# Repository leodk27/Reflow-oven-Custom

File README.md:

# Reflow Oven Controller  

### KES – Kwas Engineering Solutions  

---

## Overview

This is a controller for a reflow oven.  

---

## System

The system has three parts:

- Measurement (temperature)  
- Control (microcontroller)  
- Power switching (heater)  

---

## Hardware

- Microcontroller  
- Thermocouple interface  
- Triac switching stage  
- Power supply (internal and external)  

---

## Firmware

- Runs the temperature profile  
- Handles faults  
- Communicates over custom RJ45 service port  

---

## Safety

- High and low voltage are separated  
- Layout respects clearance  
- Faults lead to shutdown  

---

## Structure

- `/KICAD reflow-oven` — KiCad files  
- `/firmware` — code  
- `/docs` — notes  

---

## License

See LICENSE file.

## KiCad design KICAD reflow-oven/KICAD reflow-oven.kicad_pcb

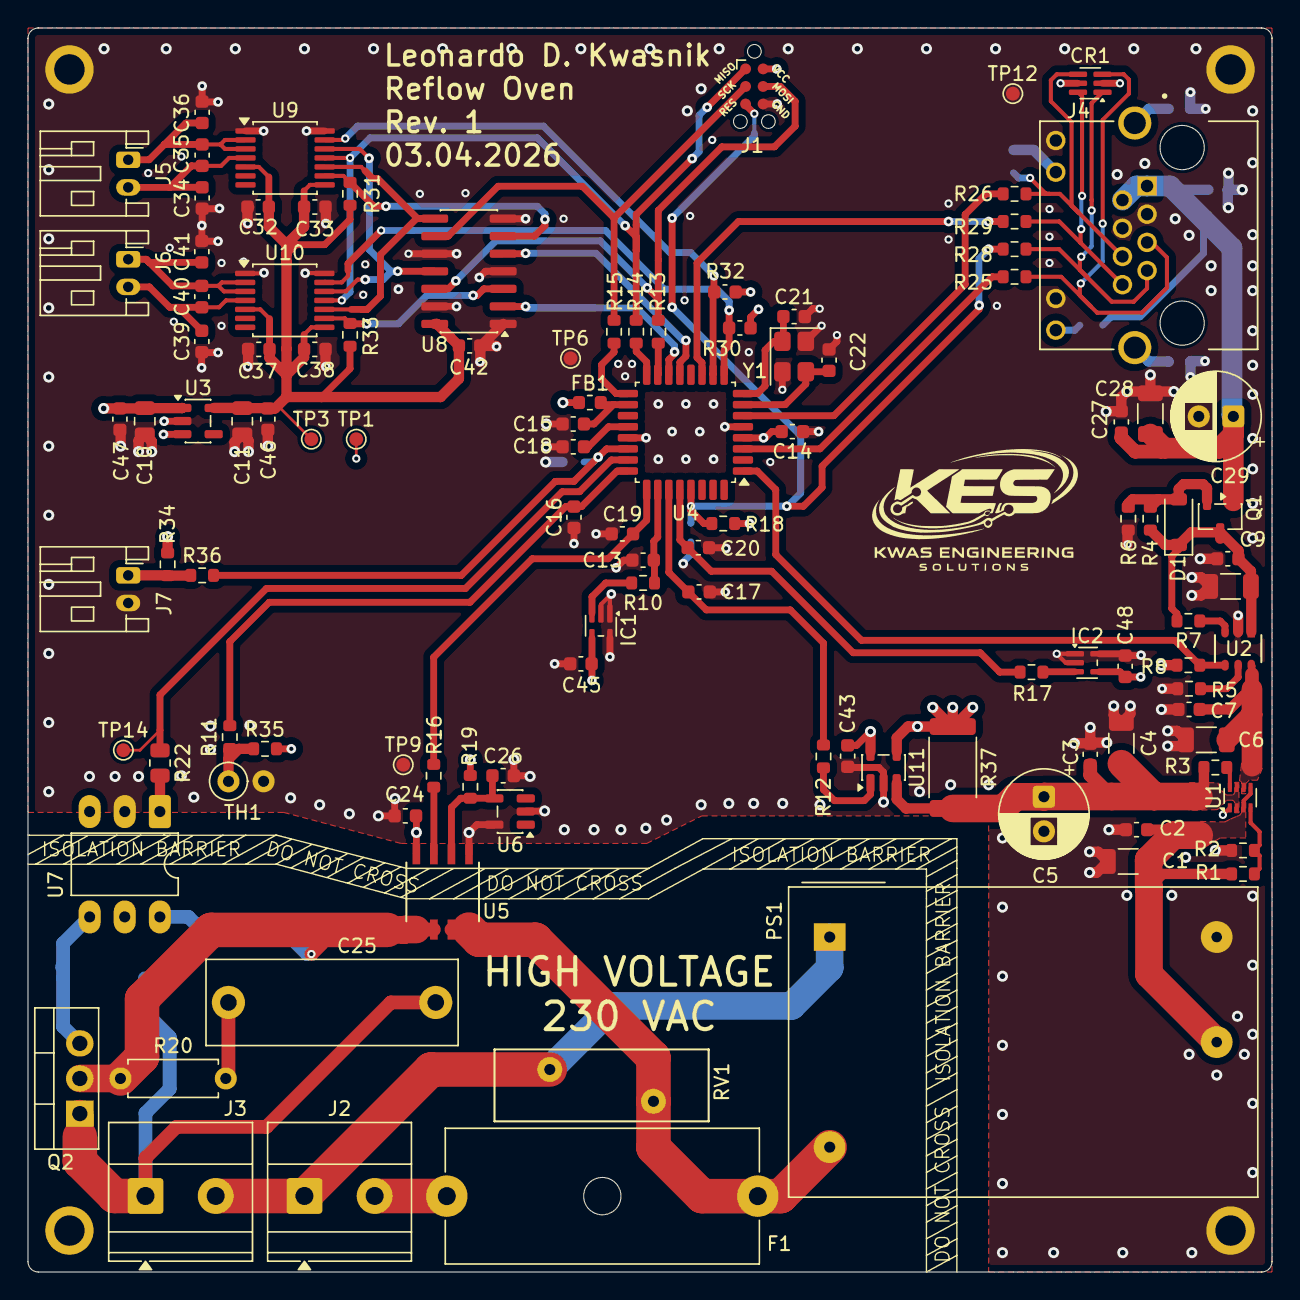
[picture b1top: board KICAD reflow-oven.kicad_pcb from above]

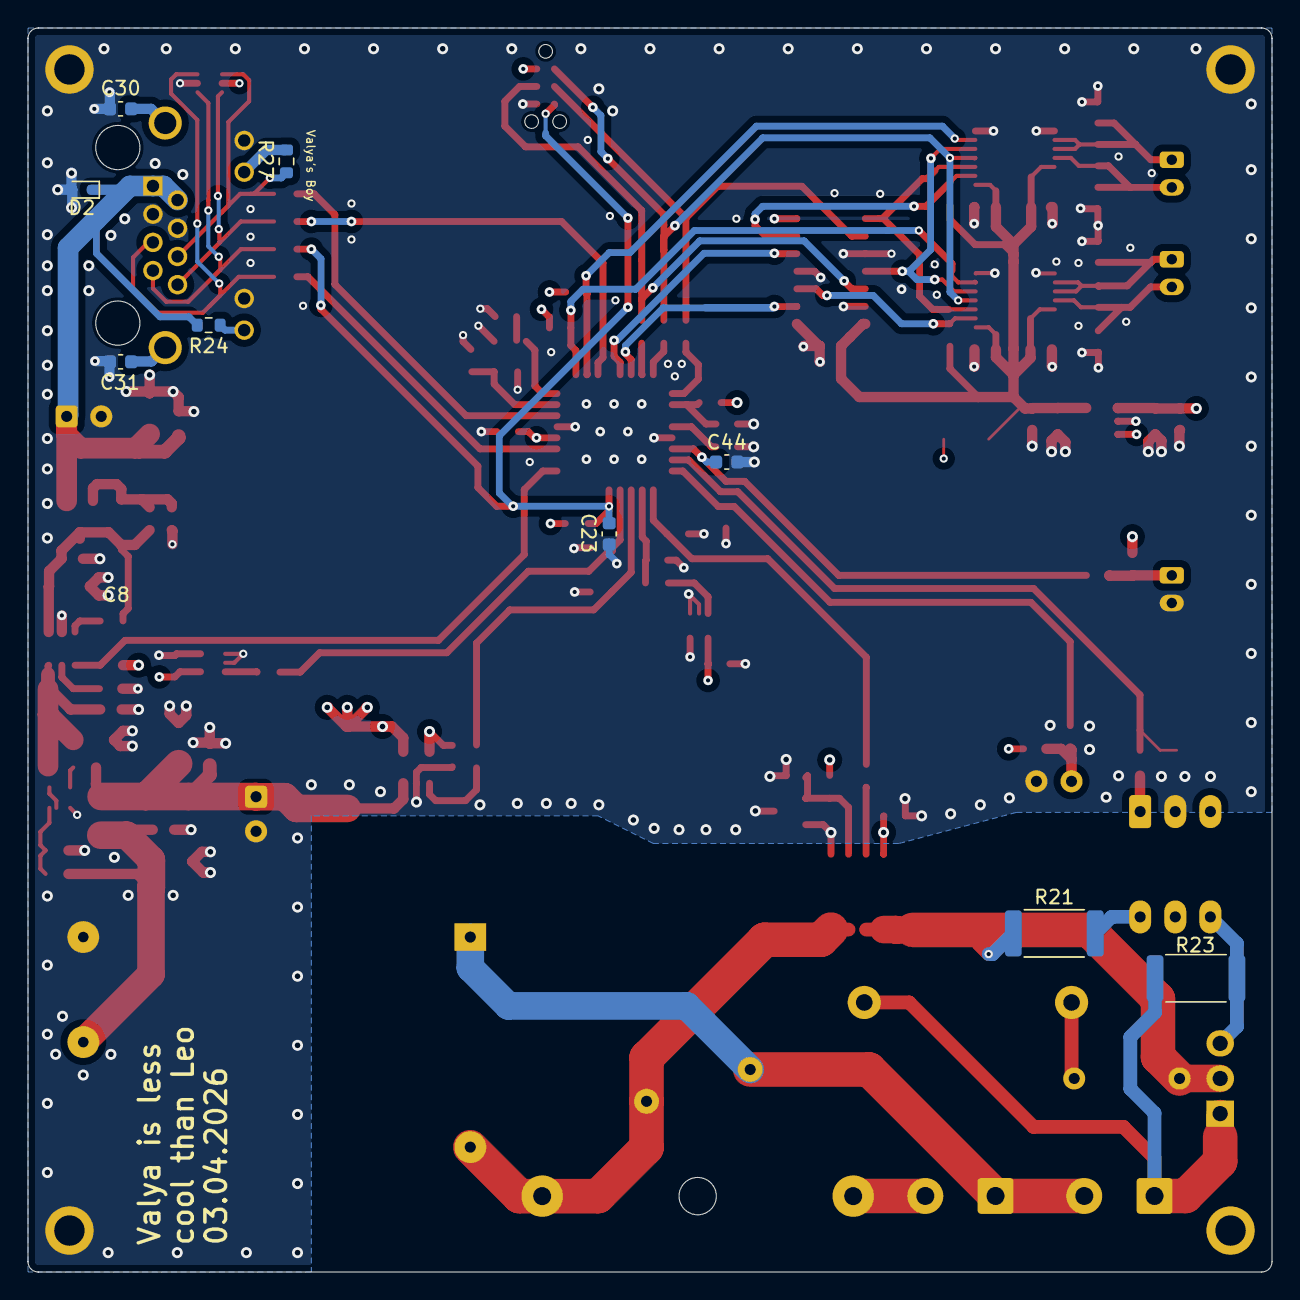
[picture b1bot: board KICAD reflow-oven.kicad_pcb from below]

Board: 4 copper layers, 90.0 x 90.0 mm, 124 parts (9 on the bottom side), 71 nets.

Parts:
C1, C4, C6, C8, C28: 10u; C_1206_3216Metric
C2, C3, C7, C9, C14, C15, C18, C24, C26, C27, C32, C33, C35, C37, C38, C40, C42, C43, C44, C45, C46, C47, C48: 100n; C_0603_1608Metric
C5, C29: 100u; CP_Radial_D6.3mm_P2.50mm
C10, C11: 1u; C_0805_2012Metric
C13, C16, C17, C19, C20, C34, C36, C39, C41: 10n; C_0603_1608Metric
C21, C22: 22p; C_0603_1608Metric
C23, C30, C31: 4.7n; C_0603_1608Metric
C25: 100n; C_Rect_L18.0mm_W6.0mm_P15.00mm_FKS3_FKP3
CR1: RCLAMP0504FBTCT; SOT-363_SC-70-6
D1: 6.8V; D_SOD-123
D2: ESD5Z5V; D_SOD-523
F1: Fuse; Fuseholder_Cylinder-5x20mm_Schurter_0031_8201_Horizontal_Op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
FB1: 600 @ 100M; L_0603_1608Metric
H1, H2, H3, H4: MountingHole_Pad; MountingHole_2.2mm_M2_ISO7380_Pad
IC1, IC2: TMP235AEDCKRQ1; SOT-353_SC-70-5
J1: KES-POGO_ISP_HEADER; KES_POGO_ISP_2x03_P1.27mm_Vertical
J2, J3: Screw_Terminal_01x02; TerminalBlock_Phoenix_MKDS-1,5-2-5.08_1x02_P5.08mm_Horizont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
J4: RJ45_LED_Shielded_SH1_SH2; ADAMTECH_MTJ-88ARX1-FSM-LG
J5, J6, J7: JST_PH; JST_PH_S2B-PH-K_1x02_P2.00mm_Horizontal
PS1: IRM-02-5; Converter_ACDC_MeanWell_IRM-02-xx_THT
Q1: PMOS; SOT-23-3
Q2: BTA16-600BW; TO-220-3_Vertical
R1: 360k; R_0603_1608Metric
R2, R4, R18: 100k; R_0603_1608Metric
R3, R6, R7, R8, R31, R33, R34, R35: 10k; R_0603_1608Metric
R5, R24, R27: 1k; R_0603_1608Metric
R10, R11, R12, R13, R14, R15, R16, R17, R25, R26, R28, R29: 100; R_0603_1608Metric
R19: 2.2k; R_0603_1608Metric
R20: 100; R_Axial_DIN0207_L6.3mm_D2.5mm_P7.62mm_Horizontal
R21, R23: 360; R_2512_6332Metric
R22: 220; R_0805_2012Metric
R30, R32: 10k; C_0603_1608Metric
R36: 470; R_0603_1608Metric
R37: 20m; R_2512_6332Metric
RV1: Varistor; RV_Disc_D15.5mm_W5.2mm_P7.5mm
TH1: 10k NTC; R_Axial_DIN0207_L6.3mm_D2.5mm_P2.54mm_Vertical
TP1: TP_5V; TestPoint_Pad_D1.0mm
TP3: TP_3V3; TestPoint_Pad_D1.0mm
TP6, TP9, TP12: TP_GND; TestPoint_Pad_D1.0mm
TP14: TP_HEAT_F; TestPoint_Pad_D1.0mm
U1: TPS2116DRL; SOT-583-8
U2: AP2553W6-7; SOT26_DIO
U3: TLV75533PDBV; SOT-23-5
U4: ATmega328PB-A; TQFP-32_7x7mm_P0.8mm
U5: TMCS1100A2QDR; SOIC8_D_TEX
U6: LM4030-2.5/NOPB; SOT-23-5
U7: MOC3063M; DIP-6_W7.62mm_LongPads
U8: 74LVC125; SOIC-14_3.9x8.7mm_P1.27mm
U9, U10: MAX31856; TSSOP-14_4.4x5mm_P0.65mm
U11: INA180A1; SOT-23-5
Y1: 16MHz; Crystal_SMD_3225-4Pin_3.2x2.5mm

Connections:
+3V3: C11.1, C32.1, C33.1, C37.1, C38.1, C42.2, C46.1, R31.1, R33.1, TP3.1, U3.5 (OUT), U8.14 (VCC), U9.5 (AVDD), U9.8 (DVDD), U10.5 (AVDD), U10.8 (DVDD)
+5V: C10.1, C14.2, C24.1, C43.1, C45.1, C47.1, C48.1, CR1.5, FB1.2, IC1.4 (VDD), IC2.4 (VDD), J1.2 (VCC), R8.2, R18.1, R19.1, R30.1, R32.1, R34.1, R35.1, R37.1, TP1.1, U3.1 (IN), U3.3 (EN), U4.4 (VCC), U5.8 (VS), U11.4 (-), U11.5 (V+)
/5V_CURRENT: R12.2, U11.1
/5V_TOSHUNT: C3.1, C4.1, C5.1, R3.1, R37.2, U1.2 (VOUT), U1.7 (VOUT), U11.3 (+)
/BOARD_TEMP1: IC1.3 (VOUT), R10.2
/BOARD_TEMP2: IC2.3 (VOUT), R17.2
/DOOR_STATUS: C44.1, R36.2, U4.22 (PE3)
/General_sensors/TO_REED: J7.1, R34.2, R36.1
/HEAT_control: R22.1, TP14.1, U4.23 (PC0)
/MAINS_CURRENT: R16.2, U5.7 (VOUT)
/MCU/AREF: C18.2, U4.20 (AREF)
/MCU/AVCC: C15.2, FB1.1, U4.18 (AVCC)
/MCU/MCU_MISO: R14.2, U4.16 (PB4)
/MCU/MCU_MOSI: R13.2, U4.15 (PB3)
/MCU/MCU_SCK: R15.2, U4.17 (PB5)
/MCU/PC1_A: C16.2, R11.1, U4.24 (PC1)
/MCU/PC2_A: C19.2, R16.1, U4.25 (PC2)
/MCU/PC3_A: C13.2, R10.1, U4.26 (PC3)
/MCU/PC4_A: C17.2, R12.1, U4.27 (PC4)
/MCU/PC5_A: C20.2, R17.1, U4.28 (PC5)
/MCU/XTAL1: C22.1, U4.7 (XTAL1/PB6), Y1.3
/MCU/XTAL2: C21.1, U4.8 (XTAL2/PB7), Y1.1
/MCU_MISO_R: J1.1 (MISO), R14.1, U9.11 (SDO), U10.11 (SDO)
/MCU_MOSI_R: J1.4 (MOSI), R13.1, U8.12
/MCU_SCK_R: J1.3 (SCK), R15.1, U8.9
/Mains_switching/AC_L_FUSED: F1.1, PS1.2 (AC/L), RV1.1, U5.3 (IN-), U5.4 (IN-)
/Mains_switching/AC_L_IN: F1.2, J2.2
/Mains_switching/AC_L_TO_HEATER: C25.2, J3.1, Q2.1 (A1), R23.1
/Mains_switching/AC_L_TO_TRIAC: Q2.2 (A2), R20.1, R21.1, U5.1 (IN+), U5.2 (IN+)
/Mains_switching/AC_N: J2.1, J3.2, PS1.1 (AC/N), RV1.2
/Mains_switching/AC_T_GATE: Q2.3 (G), R23.2, U7.4
/Mains_switching/OPTOT_LED: R22.2, U7.1
/Mains_switching/OPTOT_OUT: R21.2, U7.6
/Mains_switching/SNUBBER: C25.1, R20.2
/Mains_switching/TMCS_VREF: C26.1, R19.2, U5.6 (VREF), U6.4 (VREF)
/Power_management/AP2553_EN: R7.1, U2.3 (EN)
/Power_management/AP2553_ILIM: R5.1, U2.5 (ILIM)
/Power_management/TPS_PR1: R1.2, R2.1, U1.4 (PR1)
/Power_management/TPS_ST: R3.2, U1.8 (ST)
/Power_management/VBUS_F1: C8.1, C9.1, D1.1 (K), Q1.3 (S), R4.1, R7.2, U2.1 (IN)
/Power_management/VBUS_F2: C6.1, C7.1, U1.6 (VIN2), U2.6 (OUT)
/Power_management/VBUS_PROT_G: D1.2 (A), Q1.2 (G), R4.2, R6.1
/RESET: C23.1, J1.5 (RESET), R18.2, R28.1, U4.29 (~RESET/PC6)
/RJ45_input/RJ45_LED_1: J4.12, R24.1
/RJ45_input/RJ45_LED_2: J4.10, R27.1
/RJ45_input/RJ45_RESET: CR1.1, J4.7, R28.2
/RJ45_input/RJ45_RX: CR1.3, J4.5, R25.2
/RJ45_input/RJ45_SERVICE: CR1.6, J4.8, R29.2
/RJ45_input/RJ45_TX: CR1.4, J4.6, R26.2, R27.2
/RJ45_input/SH1: C31.2, J4.SH1
/RJ45_input/SH2: C30.2, J4.SH2
/SERVICE_IO: R29.1, U4.11 (PD7)
/TC1_CS: U4.14 (PB2), U8.2
/TC1_FAULT: R30.2, U4.10 (PD6), U9.13 (~FAULT)
/TC2_CS: U4.13 (PB1), U8.5
/TC2_FAULT: R32.2, U4.9 (PD5), U10.13 (~FAULT)
/TRIAC_TEMP: R11.2, R35.2, TH1.1
/Thermocouple_inputs/MAX_MOSI: U8.11, U9.12 (SDI), U10.12 (SDI)
/Thermocouple_inputs/MAX_SCK: U8.8, U9.10 (SCK), U10.10 (SCK)
/Thermocouple_inputs/TC1_CS_MAX: R33.2, U8.3, U10.9 (~CS)
/Thermocouple_inputs/TC2_CS_MAX: R31.2, U8.6, U9.9 (~CS)
/Thermocouple_inputs/TC_1_T+: C34.2, C35.1, J5.2, U9.4 (T+)
/Thermocouple_inputs/TC_1_T-: C35.2, C36.1, J5.1, U9.2 (BIAS), U9.3 (T-)
/Thermocouple_inputs/TC_2_T+: C39.2, C40.1, J6.2, U10.4 (T+)
/Thermocouple_inputs/TC_2_T-: C40.2, C41.1, J6.1, U10.2 (BIAS), U10.3 (T-)
/UART1_RX: R25.1, U4.3 (PE0)
/UART1_TX: R26.1, U4.6 (PE1)
/VBUS: C27.2, C28.1, C29.1, D2.1 (K), J4.1, J4.2, Q1.1 (D), R24.2
/VBUS_FAULT: R8.1, U2.4 (FAULT), U4.1 (PD3)
/VPSU: C1.1, C2.1, PS1.4 (+Vo), R1.1, U1.3 (VIN1), U1.5 (MODE)
GND: C1.2, C2.2, C3.2, C4.2, C5.2, C6.2, C7.2, C8.2, C9.2, C10.2, C11.2, C13.1, C14.1, C15.1, C16.1, C17.1, C18.1, C19.1, C20.1, C21.2, C22.2, C23.2, C24.2, C26.2, C27.1, C28.2, C29.2, C30.1, C31.1, C32.2, C33.2, C34.1, C36.2, C37.2, C38.2, C39.1, C41.2, C42.1, C43.2, C44.2, C45.2, C46.2, C47.2, C48.2, CR1.2, D2.2 (A), H1.1, H2.1, H4.1, IC1.1 (NC), IC1.2 (GND), IC1.5 (NC), IC2.1 (NC), IC2.2 (GND), IC2.5 (NC), J1.6 (GND), J4.3, J4.4, J4.9, J4.11, J7.2, PS1.3 (-Vo), R2.2, R5.2, R6.2, TH1.2, TP6.1, TP9.1, TP12.1, U1.1 (GND), U2.2 (GND), U3.2 (GND), U4.5 (GND), U4.21 (GND), U5.5 (GND), U6.2 (NC), U6.5 (GND), U7.2, U8.1, U8.4, U8.7 (GND), U8.10, U8.13, U9.1 (AGND), U9.14 (DGND), U10.1 (AGND), U10.14 (DGND), U11.2 (GND), Y1.2 (G), Y1.4 (G)

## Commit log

2026-04-06 Rename .gitignore.txt to .gitignore
2026-04-06 Update .gitignore for KiCad and OS junk files
2026-04-06 cleanup
2026-04-06 Extra file cleanup
2026-04-06 Add placeholder content to README.md
2026-04-06 ADD license and README
2026-04-06 Further cleaning
2026-04-06 Cleaning
2026-04-06 Final cleanup 06.04.2025
